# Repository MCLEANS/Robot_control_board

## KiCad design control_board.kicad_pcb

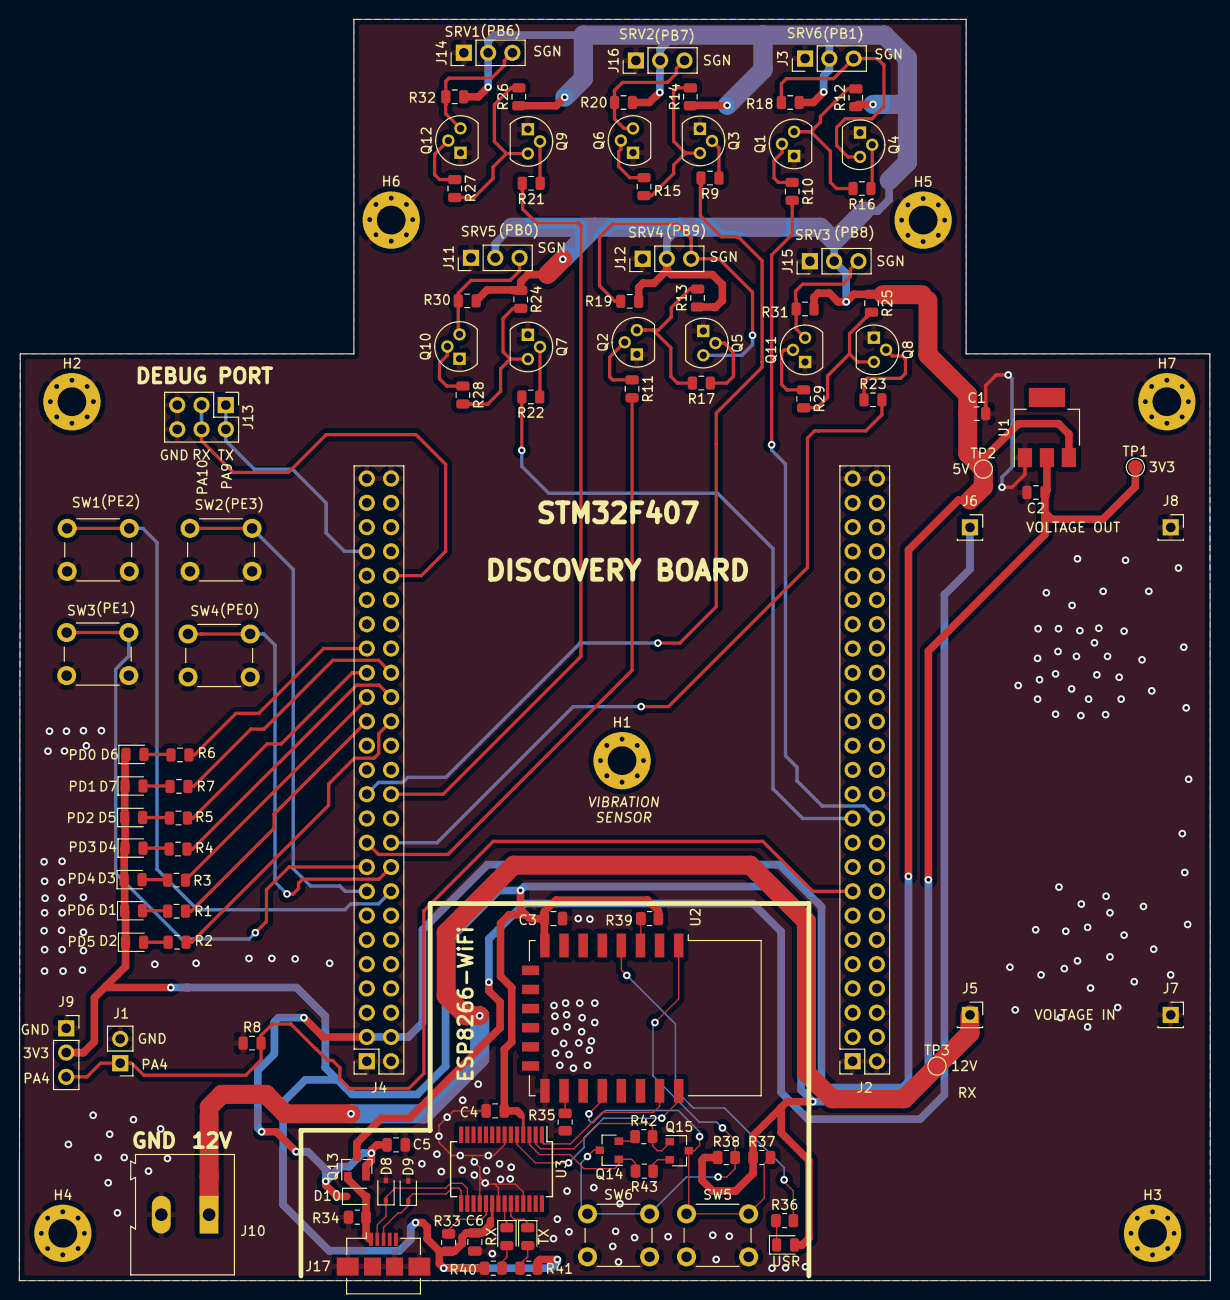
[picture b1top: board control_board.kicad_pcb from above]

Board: 2 copper layers, 124.6 x 131.9 mm, 113 parts (0 on the bottom side), 76 nets.

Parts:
C1, C2, C5: 10uF; C_0805_2012Metric
C3, C4, C6: 100nF; C_0805_2012Metric
D1, D2, D3, D4, D5, D6, D7: LED; LED_0805_2012Metric
D8, D9: 1N4448WS; D_SOD-323
D10: 1N4148WS; D_SOD-323
H1, H2, H3, H4, H5, H6, H7: MountingHole_Pad; MountingHole_3mm_Pad_Via
J1: Conn_01x02_Female; PinHeader_1x02_P2.54mm_Vertical
J2, J4: Conn_02x25_Odd_Even; PinSocket_2x25_P2.54mm_Vertical
J3, J11, J12, J14, J15, J16: Conn_01x03; PinHeader_1x03_P2.54mm_Vertical
J5, J6, J7, J8: Conn_01x01; PinSocket_1x01_P2.54mm_Vertical
J9: Conn_01x03; PinSocket_1x03_P2.54mm_Vertical
J10: Screw_Terminal_01x02; TerminalBlock_Altech_AK300-2_P5.00mm
J13: Conn_02x03_Odd_Even; PinHeader_2x03_P2.54mm_Vertical
J17: USB_B_Micro; USB_Micro-B_Amphenol_10104110_Horizontal
Q1, Q2, Q3, Q4, Q5, Q6, Q7, Q8, Q9, Q10, Q11, Q12: 2N2219; TO-92
Q13: BSS84; SOT-23
Q14, Q15: S8050; SOT-23
R1, R2, R3, R4, R5, R6, R7: 220; R_0805_2012Metric
R8: 1M; R_0805_2012Metric
R9, R10, R11, R12, R13, R14, R15, R16, R17, R18, R19, R20, R21, R22, R23, R24, R25, R26, R27, R28, R29, R30, R31, R32: 1K; R_0805_2012Metric
R33, R35, R37, R38, R39, R42, R43: 10K; R_0805_2012Metric
R34: 100K; R_0805_2012Metric
R36, R40, R41: 200; R_0805_2012Metric
RX: LED; LED_0805_2012Metric
SW1, SW2, SW3, SW4, SW5, SW6: SW_Push; SW_PUSH_6mm
TP1, TP2, TP3: TestPoint; TestPoint_Pad_D1.5mm
TX: LED; LED_0805_2012Metric
U1: LM1117-3.3; SOT-223
U2: ESP-12E
U3: FT232RL; SSOP-28_5.3x10.2mm_P0.65mm
USR: LED; LED_0805_2012Metric

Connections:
+3V3: C2.1, C3.2, C4.1, C6.1, D1.1, D2.1, D3.1, D4.1, D5.1, D6.1, D7.1, J9.2, R33.2, R37.1, R38.1, R39.1, R40.1, R41.1, TP1.1, U1.2, U2.8, U3.4, U3.20, USR.2
+5V: C1.1, C5.1, D10.1, J3.2, J4.3, J4.4, J11.2, J12.2, J14.2, J15.2, J16.2, Q13.2, R12.1, R13.1, R14.1, R18.1, R19.1, R20.1, R24.1, R25.1, R26.1, R30.1, R31.1, R32.1, TP2.1, U1.3
+12V: J5.1, J10.1, TP3.1
D+: D9.1, J17.3, U3.15
D-: D8.1, J17.2, U3.16
DEBUG_RX: J4.42, J13.3, J13.4
DEBUG_TX: J4.43, J13.1, J13.2
DTR: Q15.1, R42.2, U3.2
ESP_EN: R39.2, U2.3
ESP_RST: Q14.3, R38.2, SW6.1, U2.1
ESP_RX: U2.21, U3.1
ESP_TX: U2.22, U3.5
GND: C1.2, C2.2, C3.1, C4.2, C5.2, C6.2, D8.2, D9.2, H2.1, H3.1, H4.1, H5.1, H6.1, H7.1, J1.2, J2.1, J2.2, J2.6, J2.24, J2.49, J2.50, J3.1, J4.1, J4.2, J4.49, J4.50, J7.1, J8.1, J9.1, J10.2, J11.1, J12.1, J13.5, J13.6, J14.1, J15.1, J16.1, J17.4, J17.5, J17.6, Q1.1, Q2.1, Q3.1, Q4.1, Q5.1, Q6.1, Q7.1, Q8.1, Q9.1, Q10.1, Q11.1, Q12.1, R8.1, R34.1, R35.1, SW1.2, SW2.2, SW3.2, SW4.2, SW5.2, SW6.2, U1.1, U2.15, U3.7, U3.18, U3.21, U3.25
GPIO0: Q15.3, R37.2, SW5.1, U2.18
GPIO15: R35.2, U2.16
GPIO16: R36.2, U2.4
unnamed: D1.2, R1.1
unnamed: D2.2, R2.1
unnamed: D3.2, R3.1
unnamed: D4.2, R4.1
unnamed: D5.2, R5.1
unnamed: D6.2, R6.1
unnamed: D7.2, R7.1
unnamed: R36.1, USR.1
unnamed: TX.1, U3.23
unnamed: R41.2, TX.2
unnamed: RX.1, U3.22
unnamed: R40.2, RX.2
unnamed: Q1.2, R10.1
unnamed: Q1.3, R12.2, R16.2
unnamed: Q2.2, R11.1
unnamed: Q2.3, R13.2, R17.2
unnamed: Q3.2, R9.1
unnamed: Q3.3, R14.2, R15.2
unnamed: Q4.2, R16.1
unnamed: Q5.2, R17.1
unnamed: Q6.2, R15.1
unnamed: Q7.2, R22.1
unnamed: Q7.3, R24.2, R28.2
unnamed: Q8.2, R23.1
unnamed: Q8.3, R25.2, R29.2
unnamed: Q9.2, R21.1
unnamed: Q9.3, R26.2, R27.2
unnamed: Q10.2, R28.1
unnamed: Q11.2, R29.1
unnamed: Q12.2, R27.1
unnamed: Q14.2, R42.1
unnamed: Q15.2, R43.1
unnamed: R33.1, U3.19
PA_4: J1.1, J2.15, J9.3, R8.2
PD_0: J4.35, R6.2
PD_1: J4.34, R7.2
PD_2: J4.33, R5.2
PD_3: J4.32, R4.2
PD_4: J4.31, R3.2
PD_5: J4.30, R2.2
PD_6: J4.29, R1.2
PE_0: J4.18, SW4.1
PE_1: J4.17, SW3.1
PE_2: J4.16, SW1.1
PE_3: J4.15, SW2.1
RTS: Q14.1, R43.2, U3.3
SRV1_3V3: J4.24, R21.2
SRV1_5V: J14.3, Q12.3, R32.2
SRV2_3V3: J4.23, R9.2
SRV2_5V: J16.3, Q6.3, R20.2
SRV3_3V3: J4.20, R23.2
SRV3_5V: J15.3, Q11.3, R31.2
SRV4_3V3: J4.19, R11.2
SRV4_5V: J12.3, Q5.3, R19.2
SRV5_3V3: J2.21, R22.2
SRV5_5V: J11.3, Q10.3, R30.2
SRV6_3V3: J2.22, R10.2
SRV6_5V: J3.3, Q4.3, R18.2
VBUS: D10.2, J17.1, Q13.1, R34.2
VIN: J6.1, Q13.3

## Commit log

2021-06-22 Added level shifting
2021-06-28 Added servo control and leds
2021-07-04 Routed board layout
2021-07-04 zipped manufacturing files
2022-03-23 added ESP8266 circuit
